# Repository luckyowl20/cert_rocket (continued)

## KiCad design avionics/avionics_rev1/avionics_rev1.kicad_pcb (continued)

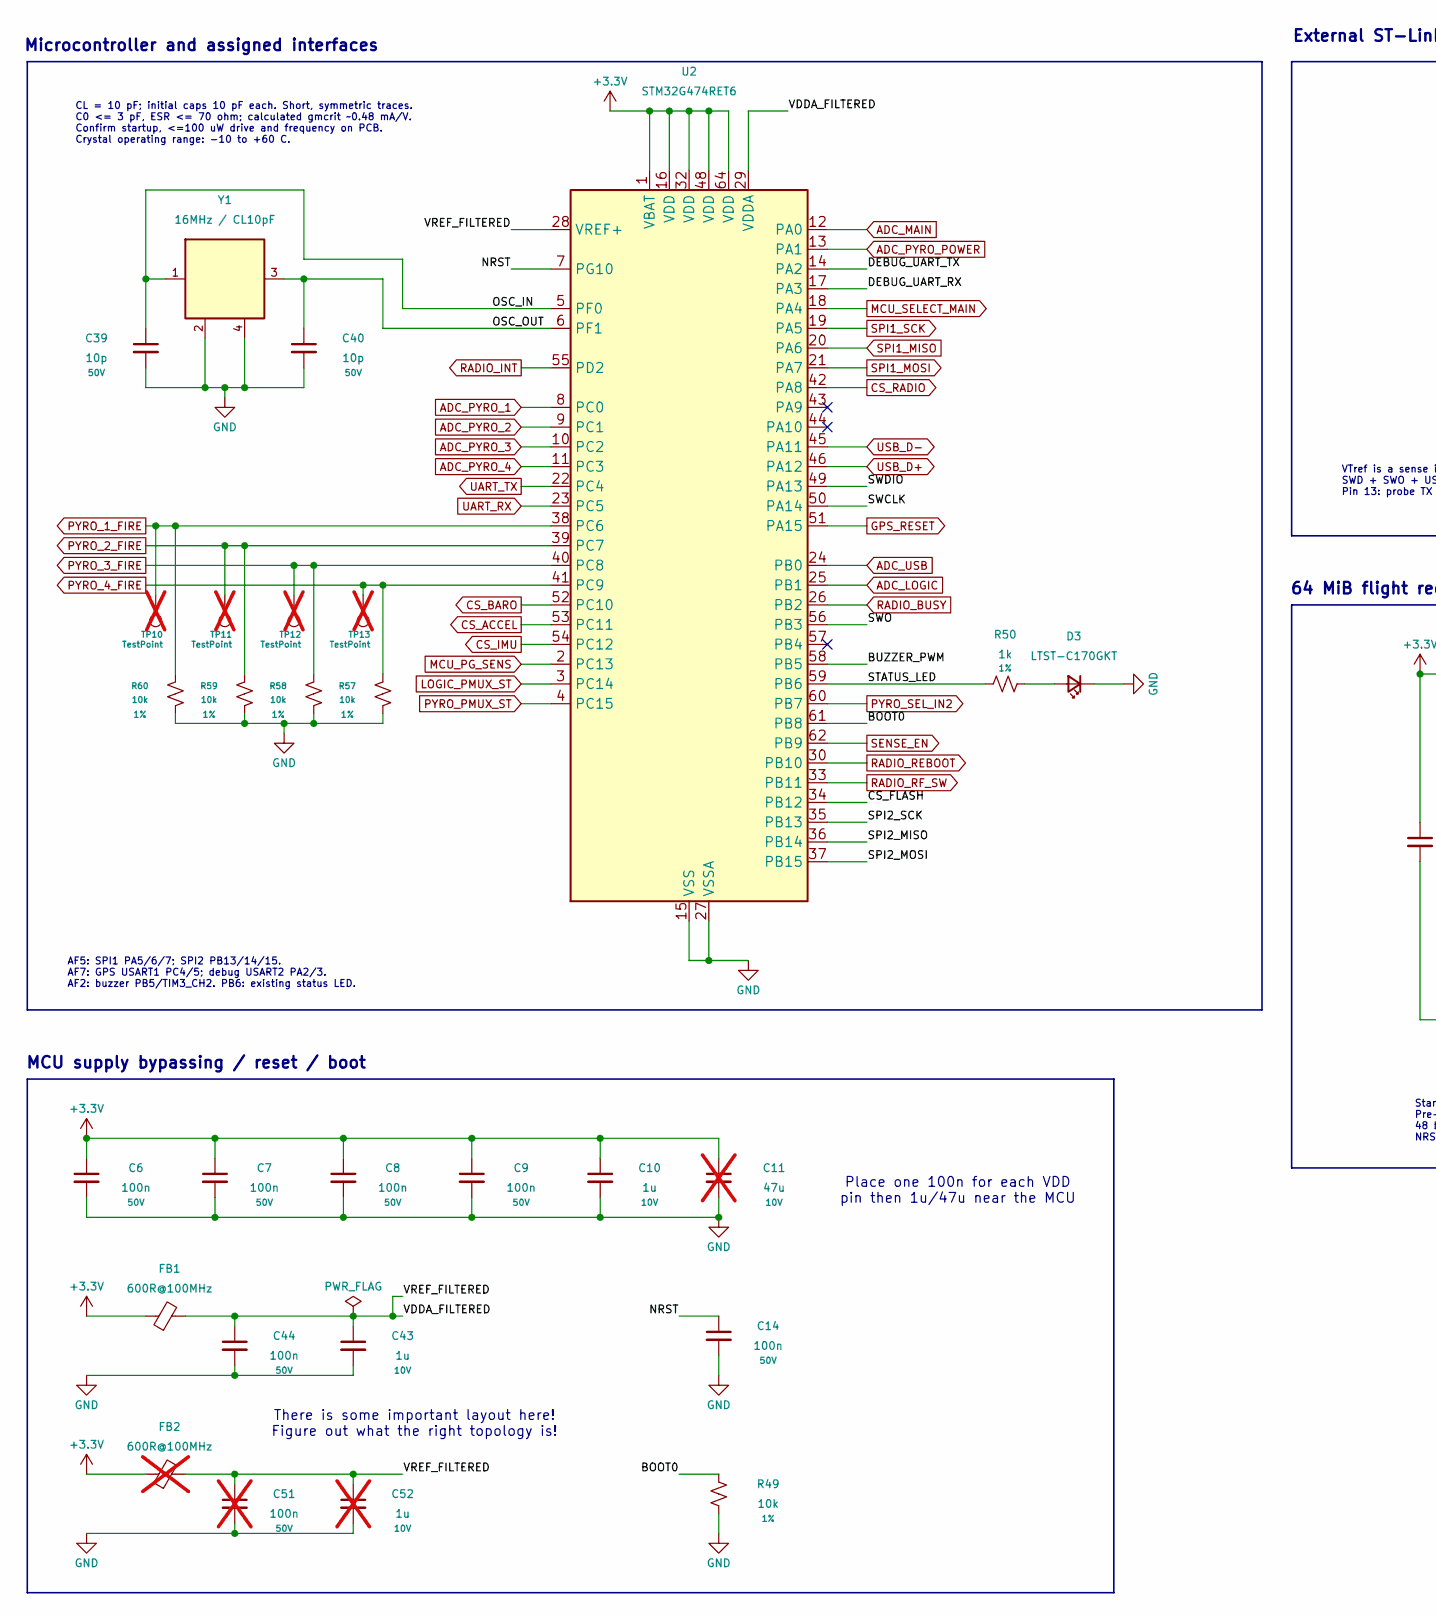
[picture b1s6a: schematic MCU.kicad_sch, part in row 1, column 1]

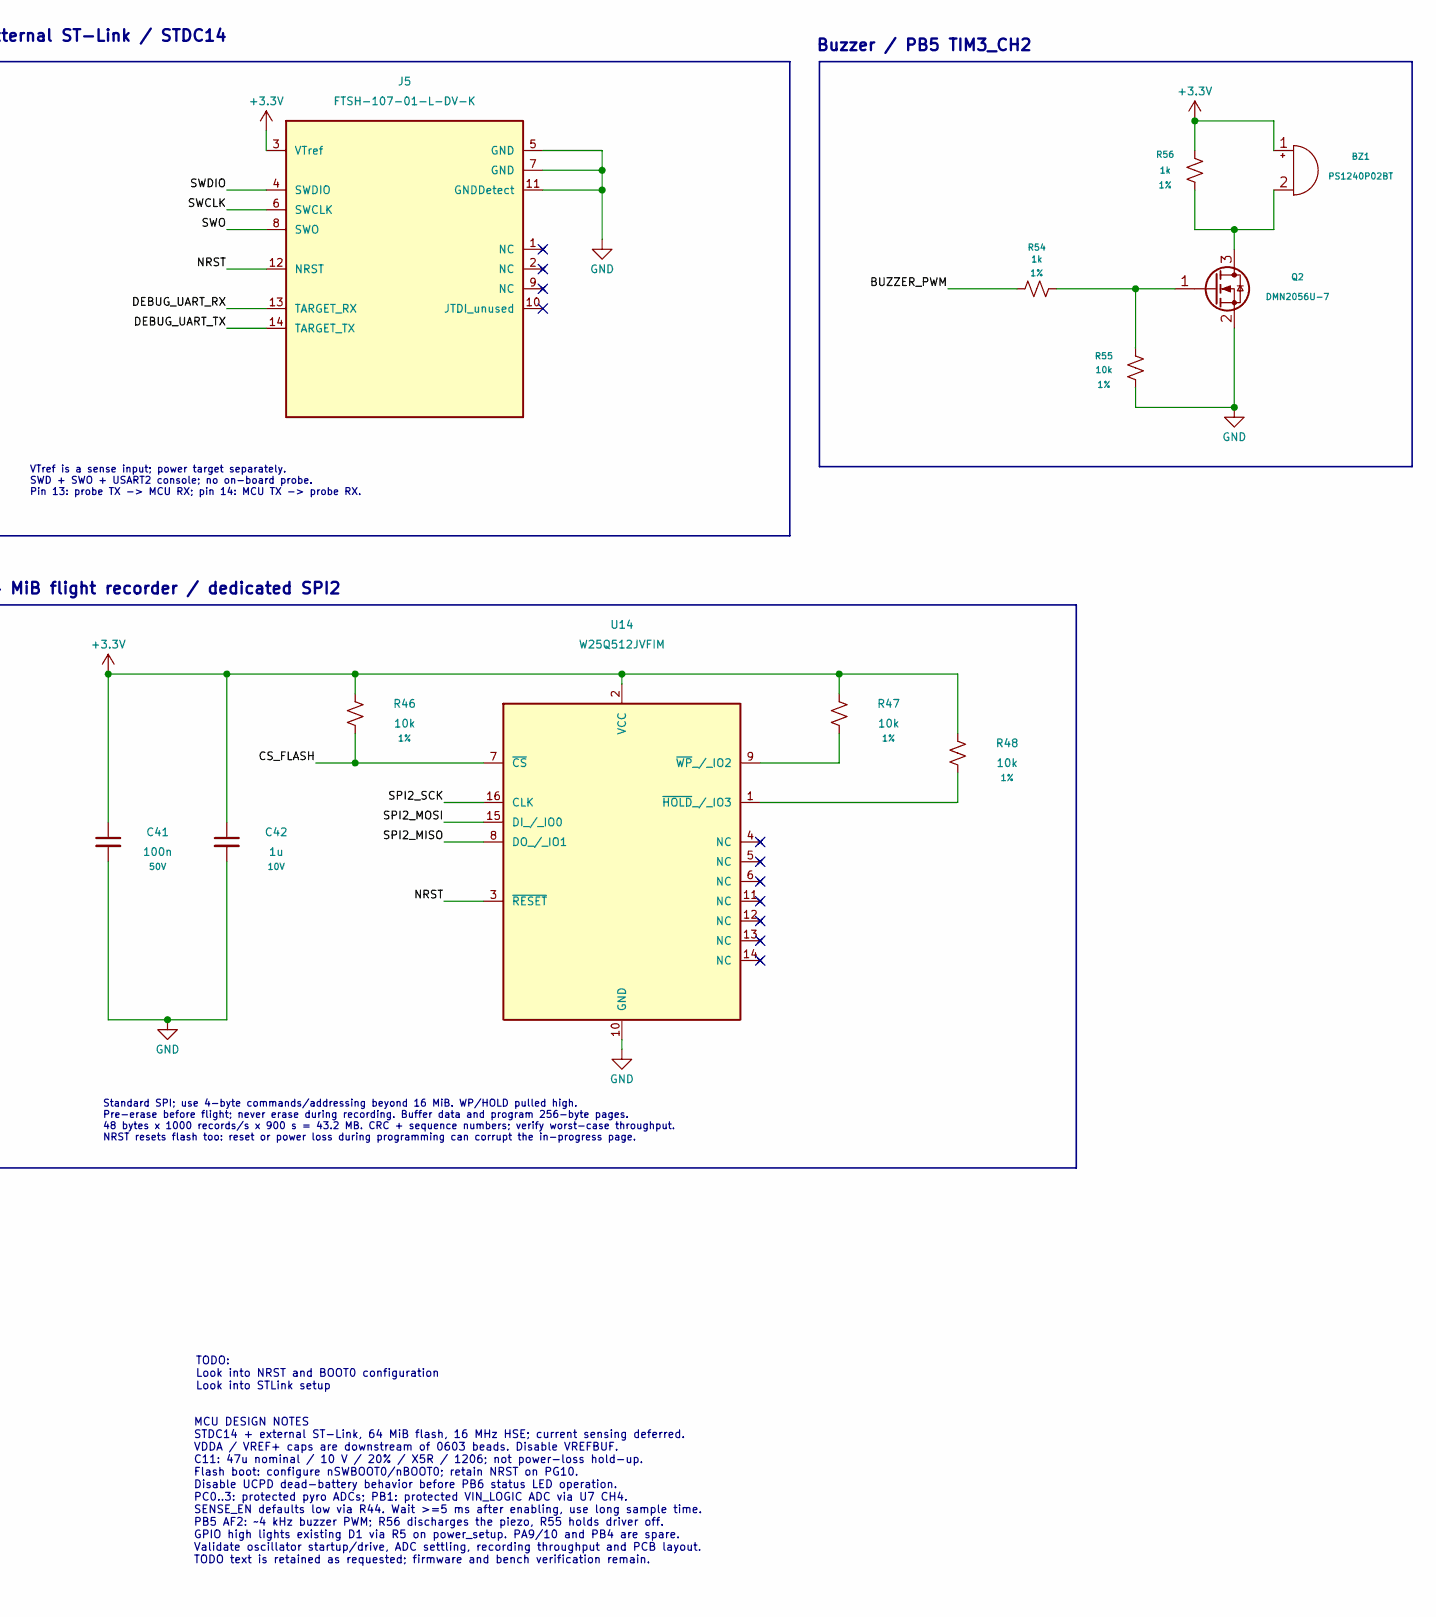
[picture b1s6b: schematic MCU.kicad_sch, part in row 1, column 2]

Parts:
BZ1: PS1240P02BT; XDCR_PS1240P02BT; MPN PS1240P02BT
C6, C7, C8, C9, C14, C41, C44: 100n; C_0603_1608Metric; Tolerance 10%; Voltage 50V; MPN C0603C104K5RACTU
C10, C42, C43: 1u; C_0603_1608Metric; Tolerance 10%; Voltage 10V; MPN C1608X7R1A105K080AC
C11: 47u; C_1206_3216Metric; Tolerance 20%; Voltage 10V; MPN C3216X5R1A476M160AB; not fitted
C39, C40: 10p; C_0603_1608Metric; Tolerance 5%; Voltage 50V; MPN C0603C100J5GACTU
C51: 100n; C_0603_1608Metric; Tolerance 10%; Voltage 50V; MPN C0603C104K5RACTU; not fitted
C52: 1u; C_0603_1608Metric; Tolerance 10%; Voltage 10V; MPN C1608X7R1A105K080AC; not fitted
D3: LTST-C170GKT; LTST_C170GKT_0805; MPN LTST-C170GKT
FB1: 600R@100MHz; L_0603_1608Metric; Impedance tolerance 25%; MPN BLM18AG601SN1D
FB2: 600R@100MHz; L_0603_1608Metric; Impedance tolerance 25%; MPN BLM18AG601SN1D; not fitted
J5: FTSH-107-01-L-DV-K; FTSH-107-01-L-DV-K_STDC14; MPN FTSH-107-01-L-DV-K
Q2: DMN2056U-7; DMN2056U_7_SOT23; MPN DMN2056U-7
R46, R47, R48, R49, R55, R57, R58, R59, R60: 10k; R_0603_1608Metric; Tolerance 1%; Voltage 75V; MPN RC0603FR-0710KL
R50, R54, R56: 1k; R_0603_1608Metric; Tolerance 1%; Voltage 75V; MPN RC0603FR-071KL
TP10, TP11, TP12, TP13: TestPoint; TestPoint_Pad_D1.0mm; not fitted
U2: STM32G474RET6; LQFP-64_10x10mm_P0.5mm; MPN STM32G474RET6
U14: W25Q512JVFIM; W25Q512JVFIM_SOIC16W; MPN W25Q512JVFIM
Y1: 16MHz / CL10pF; ABM8_3.2x2.5mm; MPN ABM8-16.000MHZ-10-1-U-T

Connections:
/MCU/BOOT0: R49.1, U2.61 (PB8)
/MCU/BUZZER_PWM: R54.1, U2.58 (PB5)
/MCU/CS_FLASH: R46.2, U2.34 (PB12), U14.7 (~CS)
/MCU/DEBUG_UART_RX: J5.13 (TARGET_RX), U2.17 (PA3)
/MCU/DEBUG_UART_TX: J5.14 (TARGET_TX), U2.14 (PA2)
/MCU/NRST: C14.1, J5.12 (NRST), U2.7 (PG10), U14.3 (~RESET)
/MCU/OSC_IN: C39.1, U2.5 (PF0), Y1.1 (OSC1)
/MCU/OSC_OUT: C40.1, U2.6 (PF1), Y1.3 (OSC2)
/MCU/SPI2_MISO: U2.36 (PB14), U14.8 (DO_/_IO1)
/MCU/SPI2_MOSI: U2.37 (PB15), U14.15 (DI_/_IO0)
/MCU/SPI2_SCK: U2.35 (PB13), U14.16 (CLK)
/MCU/STATUS_LED: R50.2, U2.59 (PB6)
/MCU/SWCLK: J5.6 (SWCLK), U2.50 (PA14)
/MCU/SWDIO: J5.4 (SWDIO), U2.49 (PA13)
/MCU/SWO: J5.8 (SWO), U2.56 (PB3)
/MCU/VDDA_FILTERED: C43.1, C44.1, C51.1, C52.1, FB1.2, FB2.2, U2.28 (VREF+), U2.29 (VDDA)
ADC_LOGIC: U2.25 (PB1); also elsewhere on the board
ADC_MAIN: U2.12 (PA0); also elsewhere on the board
ADC_PYRO_1: U2.8 (PC0); also elsewhere on the board
ADC_PYRO_2: U2.9 (PC1); also elsewhere on the board
ADC_PYRO_3: U2.10 (PC2); also elsewhere on the board
ADC_PYRO_4: U2.11 (PC3); also elsewhere on the board
ADC_PYRO_POWER: U2.13 (PA1); also elsewhere on the board
ADC_USB: U2.24 (PB0); also elsewhere on the board
CS_ACCEL: U2.53 (PC11); also elsewhere on the board
CS_BARO: U2.52 (PC10); also elsewhere on the board
CS_IMU: U2.54 (PC12); also elsewhere on the board
CS_RADIO: U2.42 (PA8); also elsewhere on the board
GND: C6.2, C7.2, C8.2, C9.2, C10.2, C11.2, C14.2, C39.2, C40.2, C41.2, C42.2, C43.2, C44.2, C51.2, C52.2, D3.1 (K), J5.5 (GND), J5.7 (GND), J5.11 (GNDDetect), Q2.2 (S), R49.2, R55.2, R57.2, R58.2, R59.2, R60.2, U2.15 (VSS), U2.27 (VSSA), U2.31 (VSS), U2.47 (VSS), U2.63 (VSS), U14.10 (GND), Y1.2 (CASE), Y1.4 (CASE); also elsewhere on the board
GPS_RESET: U2.51 (PA15); also elsewhere on the board
LOGIC_PMUX_ST: U2.3 (PC14); also elsewhere on the board
MCU_PG_SENS: U2.2 (PC13); also elsewhere on the board
MCU_SELECT_MAIN: U2.18 (PA4); also elsewhere on the board
unnamed: BZ1.2 (-), Q2.3 (D), R56.2
unnamed: D3.2 (A), R50.1
unnamed: Q2.1 (G), R54.2, R55.1
unnamed: R48.2, U14.1 (~HOLD_/_IO3)
unnamed: R47.2, U14.9 (~WP_/_IO2)
PYRO_1_FIRE: R60.1, TP10.1, U2.38 (PC6); also elsewhere on the board
PYRO_2_FIRE: R59.1, TP11.1, U2.39 (PC7); also elsewhere on the board
PYRO_3_FIRE: R58.1, TP12.1, U2.40 (PC8); also elsewhere on the board
PYRO_4_FIRE: R57.1, TP13.1, U2.41 (PC9); also elsewhere on the board
PYRO_PMUX_ST: U2.4 (PC15); also elsewhere on the board
PYRO_SEL_IN2: U2.60 (PB7); also elsewhere on the board
RADIO_BUSY: U2.26 (PB2); also elsewhere on the board
RADIO_INT: U2.55 (PD2); also elsewhere on the board
RADIO_REBOOT: U2.30 (PB10); also elsewhere on the board
RADIO_RF_SW: U2.33 (PB11); also elsewhere on the board
SENSE_EN: U2.62 (PB9); also elsewhere on the board
SPI1_MISO: U2.20 (PA6); also elsewhere on the board
SPI1_MOSI: U2.21 (PA7); also elsewhere on the board
SPI1_SCK: U2.19 (PA5); also elsewhere on the board
UART_RX: U2.23 (PC5); also elsewhere on the board
UART_TX: U2.22 (PC4); also elsewhere on the board
USB_D+: U2.46 (PA12); also elsewhere on the board
USB_D-: U2.45 (PA11); also elsewhere on the board

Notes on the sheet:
AF5: SPI1 PA5/6/7; SPI2 PB13/14/15. AF7: GPS USART1 PC4/5; debug USART2 PA2/3. AF2: buzzer PB5/TIM3_CH2. PB6: existing status LED.
Place one 100n for each VDD pin then 1u/47u near the MCU
CL = 10 pF; initial caps 10 pF each. Short, symmetric traces. C0 <= 3 pF, ESR <= 70 ohm; calculated gmcrit ~0.48 mA/V. Confirm startup, <=100 uW drive and frequency on PCB. Crystal operating range: -10 to +60 C.
MCU supply bypassing / reset / boot
MCU DESIGN NOTES STDC14 + external ST-Link, 64 MiB flash, 16 MHz HSE; current sensing deferred. VDDA / VREF+ caps are downstream of 0603 beads. Disable VREFBUF. C11: 47u nominal / 10 V / 20% / X5R / 1206; not power-loss hold-up. Flash boot: configure nSWBOOT0/nBOOT0; retain NRST on PG10. Disable UC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
Standard SPI; use 4-byte commands/addressing beyond 16 MiB. WP/HOLD pulled high. Pre-erase before flight; never erase during recording. Buffer data and program 256-byte pages. 48 bytes x 1000 records/s x 900 s = 43.2 MB. CRC + sequence numbers; verify worst-case throughput. NRST resets flash too: r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
External ST-Link / STDC14
TODO: Look into NRST and BOOT0 configuration Look into STLink setup
Microcontroller and assigned interfaces
VTref is a sense input; power target separately. SWD + SWO + USART2 console; no on-board probe. Pin 13: probe TX -> MCU RX; pin 14: MCU TX -> probe RX.
There is some important layout here! Figure out what the right topology is!
Buzzer / PB5 TIM3_CH2
64 MiB flight recorder / dedicated SPI2

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
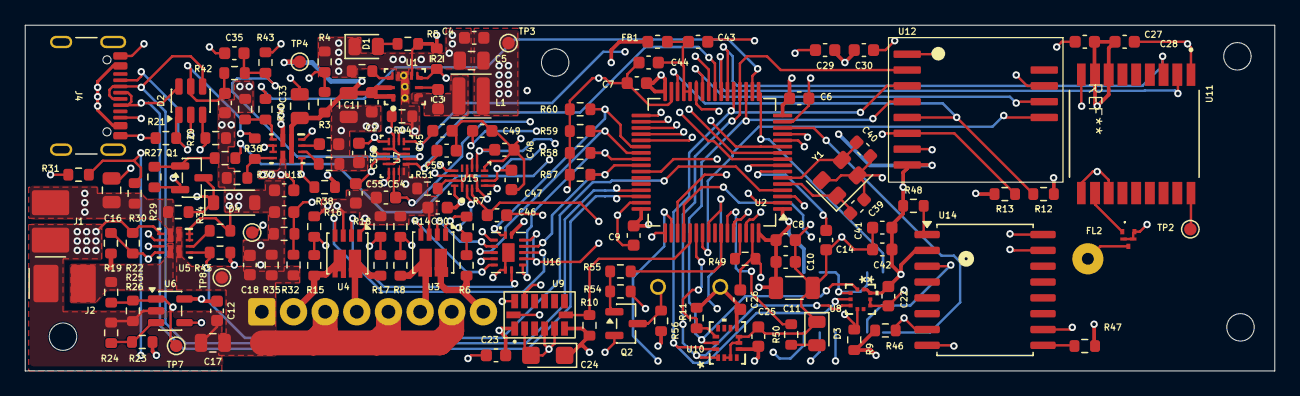
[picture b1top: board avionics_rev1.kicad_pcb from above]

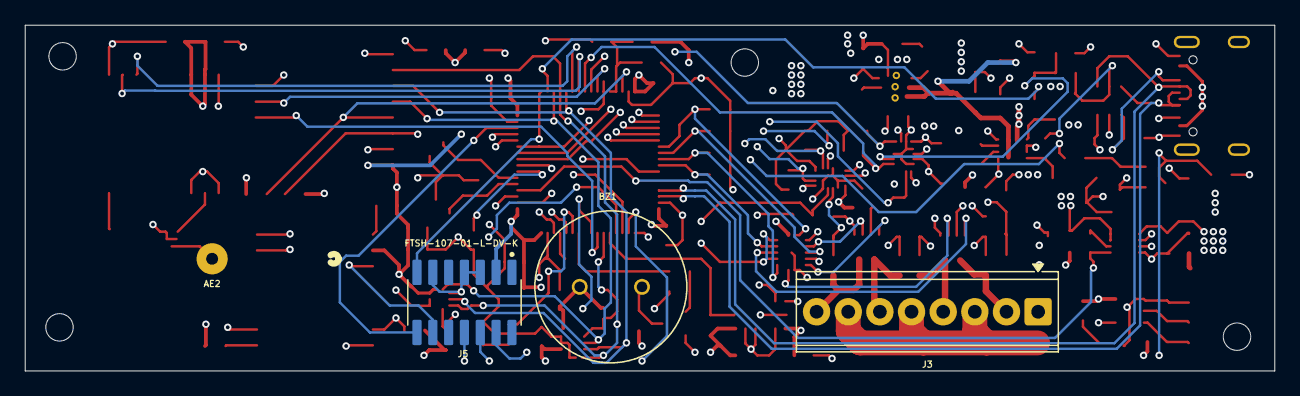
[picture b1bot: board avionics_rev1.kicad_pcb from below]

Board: 4 copper layers, 100.3 x 27.7 mm, 148 parts (4 on the bottom side), 97 nets.

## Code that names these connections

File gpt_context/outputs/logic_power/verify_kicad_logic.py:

"""Check actual KiCad-exported nets, not just drawing coordinates."""
import json
import sys
from pathlib import Path
from kicad_block import parse, child, children, unq, HERE

netfile = Path(sys.argv[1]) if len(sys.argv) > 1 else HERE / 'logic_mux_block.net'
doc = parse(netfile.read_text(encoding='utf-8'))
nets = {}
for net in children(child(doc, 'nets'), 'net'):
    name = unq(child(net, 'name')[1])
    nets[name] = {(unq(child(n, 'ref')[1]), unq(child(n, 'pin')[1])) for n in children(net, 'node')}
roles = json.loads((HERE / 'kicad_block_refs.json').read_text())
u = roles['logic_mux']
def node(role, pin): return (roles[role], str(pin))
expected = {
    'VIN_USB': {(u,'7'), node('USB_input',1),node('USB_priority_upper',1),node('USB_adc_upper',1)},
    'VIN_MAIN_BATT': {(u,'2'),node('main_input',1)},
    'VIN_LOGIC': {(u,'1'),(u,'8'),node('mux_output',1)},
    'GND': {(u,'4'),(u,'5'),(u,'12'), *[node(r,2) for r in ['USB_priority_lower','USB_input','main_input','mux_output','current_limit','soft_start','override_pulldown','USB_adc_lower','USB_adc_filter','sense_enable_pulldown','TMUX_bypass']]},
    '+3.3V': {node('status_pullup',1),node('TMUX_bypass',1)},
    'LOGIC_PMUX_ST': {(u,'9'),node('status_pullup',2)},
    'MCU_SELECT_MAIN': {node('override_series',2)},
    'USB_POWER_SENS': {node('USB_adc_upper',2),node('USB_adc_lower',1),node('USB_adc_filter',1)},
    'SENSE_EN': {node('sense_enable_pulldown',1)},
}
for name, nodes in expected.items():
    assert nodes <= nets.get(name,set()), (name, nodes - nets.get(name,set()))
for nodes in [
    {(u,'6'),node('USB_priority_upper',2),node('USB_priority_lower',1)},
    {(u,'3'),node('override_series',1),node('override_pulldown',1)},
    {(u,'10'),node('current_limit',1)},
    {(u,'11'),node('soft_start',1)},
]:
    assert any(nodes == actual for actual in nets.values()), nodes
assert len({name for name,nodes in nets.items() if (u,'7') in nodes}) == 1
for pin, name in [('7','VIN_USB'),('2','VIN_MAIN_BATT'),('1','VIN_LOGIC'),('8','VIN_LOGIC')]:
    assert [n for n, pins in nets.items() if (u,pin) in pins] == [name]
assert len({frozenset(nets[n]) for n in ['VIN_USB','VIN_MAIN_BATT','VIN_LOGIC','GND','+3.3V']}) == 5
if len(sys.argv)>2 and sys.argv[2]=='--integrated':
    extra={
        'VIN_USB': {('J4','A4')},
        'VIN_MAIN_BATT': {('J1','2'),('R30','1'),('U5','2')},
        'VIN_LOGIC': {('U1','1')},
        '+3.3V': {('U7','16')},
        'GND': {('U7','8'),('U7','13'),('U7','14'),('U7','15')},
        'PYRO_POWER_SENS': {('U7','2')},
        'MAIN_BAT_SENS': {('U7','5')},
        'USB_POWER_SENS': {('U7','10')},
        'ADC_TPS_OUT': {('U7','3')},
        'ADC_MAIN': {('U7','6')},
        'ADC_USB': {('U7','9')},
        'SENSE_EN': {('U7','1'),('U7','4'),('U7','11')},
    }
    for name,nodes in extra.items():
        assert nodes <= nets.get(name,set()), (name,nodes-nets.get(name,set()))
print(f'PASS: {len(expected)+4} logic-mux groups, exact internal nets, and distinct power rails checked in {netfile.name}')
if len(sys.argv)>2 and sys.argv[2]=='--integrated':
    print(f'PASS: {len(extra)} integration groups checked, including U7 and J1')

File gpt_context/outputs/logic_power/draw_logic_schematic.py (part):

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    s.text(2270, 1710, 'SEL1/2/3 = pins 1/4/11\n16 VDD = 3V3; 8 GND = GND\n13/14/15 = GND; 7/12 = NC', 20)
    s.box(2850, 1240, 320, 600, fill=draw.LIGHT)
    s.text(2870, 1260, 'STM32G474RET6', 25, True)
    for y, label in [(1350, 'ADC_TPS_OUT'), (1480, 'ADC_MAIN'), (1630, 'ADC_USB')]:
        wire([(2660, y), (2850, y)])
        s.text(2870, y-16, label, 22, True)
    s.text(2870, 1710, 'ADC pads not assigned.\nAll channels share\nSENSE_EN.', 22)
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    s.net(1730, 1630, 'USB_DIV')
    wire([(2450, 1840), (2450, 1910), (3010, 1910), (3010, 1840)])
    s.net(2560, 1910, 'SENSE_EN')
    s.text(90, 1840, 'Shared U3: reuse existing C8 (100 nF) and R17 (100 kΩ SENSE_EN pull-down).\nChannel 3 is no longer grounded: pin 10 = USB_DIV, pin 9 = ADC_USB, pin 11 = SENSE_EN.\nThe companion pyro sheet / manifest are updated to match; only one U3 is populated.', 24)
    s.text(90, 2000, 'R24/R25: 0.1%; R18–R23: 1%. U5 and C13 removed. R18/R20/R21 changed. See README before updating an earlier schematic.', 22)
    s.text(90, 2045, 'This powers logic only. Fixed-5-V USB current authorization and input protection remain USB-front-end requirements. See README for limits.', 22, color=POWER)
    s.text(90, 2088, 'Dot = junction. Jump = no connection. Repeated net names connect across sheets. Common GND. No pyro battery feeds this mux.', 22)
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
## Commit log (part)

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2026-06-19 flight computer schematics work + 1 stage simulation
2026-06-20 updated sims
2026-06-30 more avionics work
